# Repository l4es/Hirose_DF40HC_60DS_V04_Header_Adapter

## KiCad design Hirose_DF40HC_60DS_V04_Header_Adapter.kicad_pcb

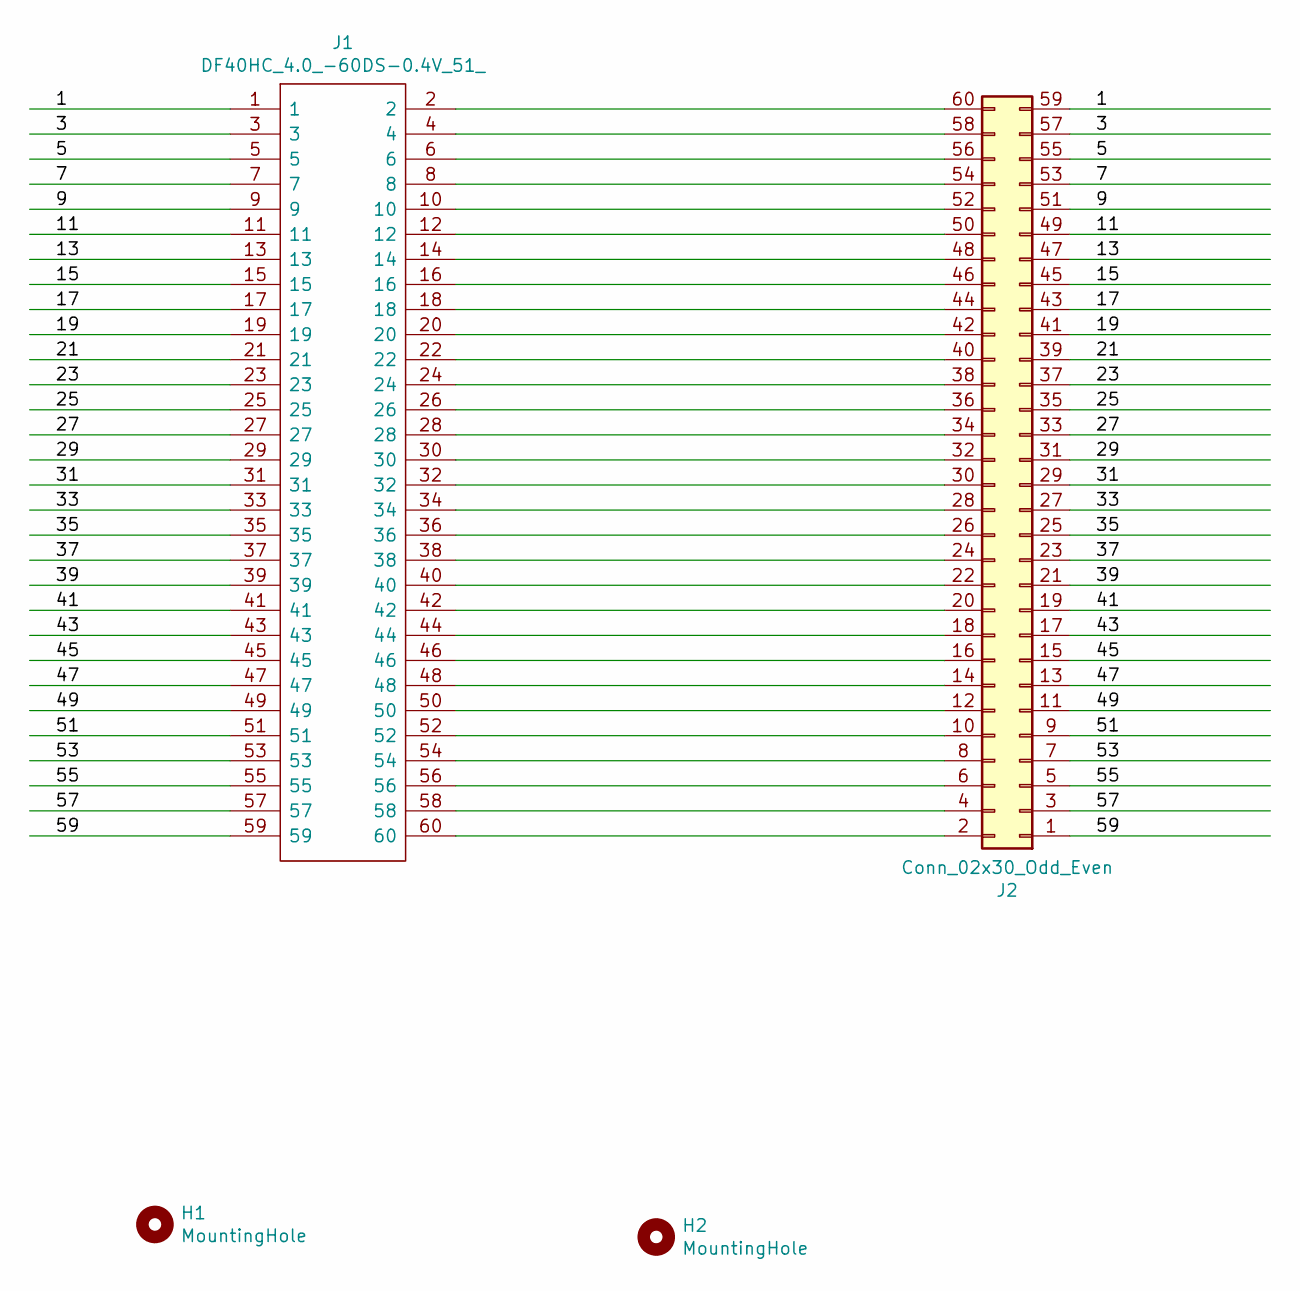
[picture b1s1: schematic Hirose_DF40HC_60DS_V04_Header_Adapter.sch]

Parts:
H1, H2: MountingHole; MountingHole_3.2mm_M3
J1: DF40HC_4.0_-60DS-0.4V_51_; DF40C-60DP-0.4V_51_; Manufacturer_Part_Number DF40HC(4.0)-60DS-0.4V(51); Mouser Part Number 798-DF4HC4060DS04V51
J2: Conn_02x30_Odd_Even; PinHeader_2x30_P2.54mm_Vertical

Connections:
/1: J1.1, J2.59
/3: J1.3, J2.57
/5: J1.5, J2.55
/7: J1.7, J2.53
/9: J1.9, J2.51
/11: J1.11, J2.49
/13: J1.13, J2.47
/15: J1.15, J2.45
/17: J1.17, J2.43
/19: J1.19, J2.41
/21: J1.21, J2.39
/23: J1.23, J2.37
/25: J1.25, J2.35
/27: J1.27, J2.33
/29: J1.29, J2.31
/31: J1.31, J2.29
/33: J1.33, J2.27
/35: J1.35, J2.25
/37: J1.37, J2.23
/39: J1.39, J2.21
/41: J1.41, J2.19
/43: J1.43, J2.17
/45: J1.45, J2.15
/47: J1.47, J2.13
/49: J1.49, J2.11
/51: J1.51, J2.9
/53: J1.53, J2.7
/55: J1.55, J2.5
/57: J1.57, J2.3
/59: J1.59, J2.1
unnamed: J1.2, J2.60
unnamed: J1.4, J2.58
unnamed: J1.6, J2.56
unnamed: J1.8, J2.54
unnamed: J1.10, J2.52
unnamed: J1.12, J2.50
unnamed: J1.14, J2.48
unnamed: J1.16, J2.46
unnamed: J1.18, J2.44
unnamed: J1.20, J2.42
unnamed: J1.22, J2.40
unnamed: J1.24, J2.38
unnamed: J1.26, J2.36
unnamed: J1.28, J2.34
unnamed: J1.30, J2.32
unnamed: J1.32, J2.30
unnamed: J1.34, J2.28
unnamed: J1.36, J2.26
unnamed: J1.38, J2.24
unnamed: J1.40, J2.22
unnamed: J1.42, J2.20
unnamed: J1.44, J2.18
unnamed: J1.46, J2.16
unnamed: J1.48, J2.14
unnamed: J1.50, J2.12
unnamed: J1.52, J2.10
unnamed: J1.54, J2.8
unnamed: J1.56, J2.6
unnamed: J1.58, J2.4
unnamed: J1.60, J2.2

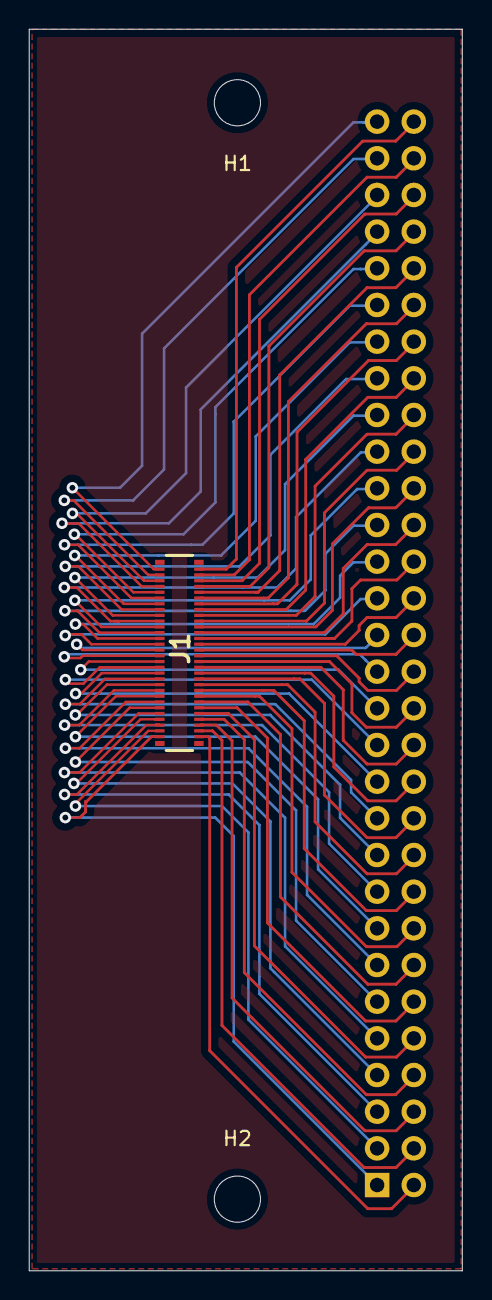
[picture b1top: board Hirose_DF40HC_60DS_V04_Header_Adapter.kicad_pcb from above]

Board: 2 copper layers, 30.0 x 86.0 mm, 4 parts (1 on the bottom side), 60 nets.

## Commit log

2021-05-25 Upload V1A
2021-05-25 Update degsign after gerbers generation
2021-11-24 Update footprints
2022-06-15 Add PDF schematic for V1A
